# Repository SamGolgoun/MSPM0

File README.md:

# MSPM0 Development Board

A compact development board built around the **Texas Instruments MSPM0G3507** Arm Cortex-M0+ microcontroller, designed in **KiCad**. The board includes USB-to-UART communication, an I2C accelerometer, and a standard SWD header for programming and debugging.

## Features

- **MCU:** TI MSPM0G3507 (LQFP-48), Arm Cortex-M0+
- **USB-C connector** with ESD protection
- **USB-UART converter:** CH340E
- **3.3 V LDO regulator** powered from USB
- **Accelerometer:** ST LIS2DH (I2C, with interrupt lines INT1/INT2)
- **8 MHz external crystal** (HFXT)
- **SWD header** (TC2030 Tag-Connect) for programming and debugging
- Decoupling and reset circuitry following manufacturer recommendations

## Schematic

## Repository Contents

| File | Description |
|------|-------------|
| `MSPM0.kicad_sch` | Schematic |
| `MSPM0.kicad_pcb` | PCB layout |
| `MSPM0.kicad_pro` | KiCad project file |
| `MSPM0-ToturialSchemSymLib.kicad_sym` | Custom symbol library |
| `sym-lib-table` | Project symbol library table |

## Getting Started

1. Install [KiCad](https://www.kicad.org/) (developed with KiCad 10).
2. Clone this repository:
   ```bash
   git clone https://github.com/SamGolgoun/MSPM0.git
   ```
3. Open `MSPM0.kicad_pro` in KiCad.
4. Make sure the project symbol library is loaded (Preferences → Manage Symbol Libraries → Project Specific Libraries).

## Status

🚧 Work in progress: schematic complete, PCB layout and routing ongoing.

## Acknowledgements

This project was created while following the [Phil's Lab](https://www.youtube.com/@PhilsLab) KiCad hardware design tutorial for the MSPM0. Many thanks for the excellent material.

## License

This project is licensed under the [MIT License](LICENSE).

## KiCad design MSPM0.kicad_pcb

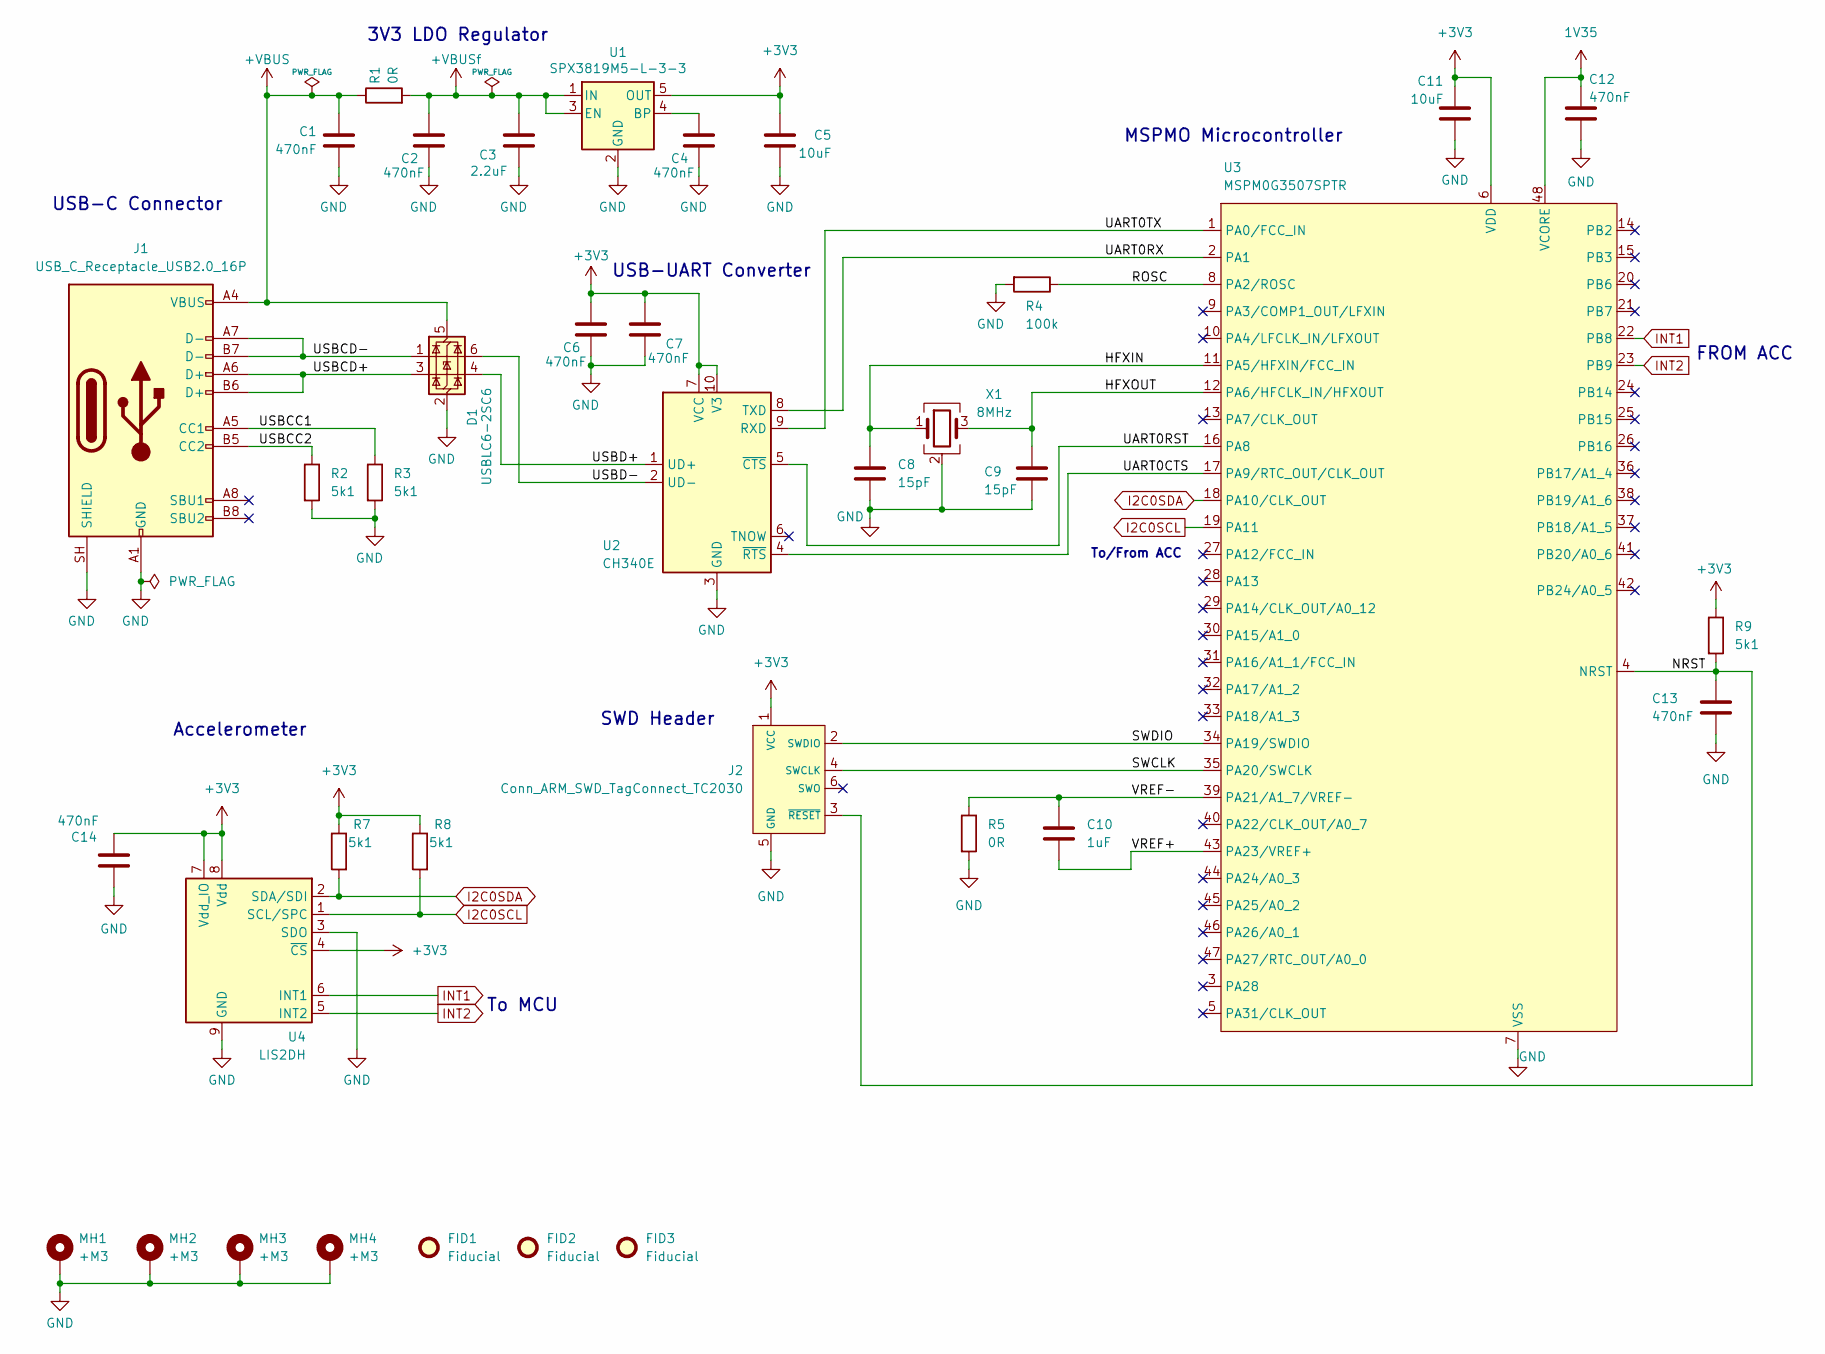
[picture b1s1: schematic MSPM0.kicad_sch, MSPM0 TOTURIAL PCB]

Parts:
C1, C2, C4, C6, C7, C12, C13, C14: 470nF; C_0603_1608Metric; Manufacturer Part Number CL10B474KA8NNNC; LCSC C1623
C3: 2.2uF; C_0805_2012Metric; Manufacturer Part Number CL21B225KAFNNNE; LCSC C19110
C5, C11: 10uF; C_0805_2012Metric; Manufacturer Part Number CL21A106KAYNNNE; LCSC C15850
C8, C9: 15pF; C_0603_1608Metric
C10: 1uF; C_0603_1608Metric; Manufacturer Part Number CL21B474KBFNNNE; LCSC C13967
D1: USBLC6-2SC6; SOT-23-6
FID1, FID2, FID3: Fiducial; Fiducial_1mm_Mask2mm
J1: USB_C_Receptacle_USB2.0_16P; USB_C_Receptacle_GCT_USB4105-xx-A_16P_TopMnt_Horizontal
J2: Conn_ARM_SWD_TagConnect_TC2030; Tag-Connect_TC2030-IDC-FP_2x03_P1.27mm_Vertical
MH1, MH2, MH3, MH4: +M3; MountingHole_3.2mm_M3_Pad_Via
R1, R5: 0R; R_0603_1608Metric
R2, R3, R7, R8, R9: 5k1; R_0603_1608Metric
R4: 100k; R_0603_1608Metric; Manufacturer Part Number RT0603BRD07100KL; LCSC C122538
U1: SPX3819M5-L-3-3; SOT-23-5
U2: CH340E; MSOP-10_3x3mm_P0.5mm
U3: MSPM0G3507SPTR; LQFP-48_7x7mm_P0.5mm; Manufacturer Part Number MSPM0G3507SPTR; LCSC C22362630
U4: LIS2DH; LGA-14_2x2mm_P0.35mm_LayoutBorder3x4y
X1: 8MHz; Crystal_SMD_3225-4Pin_3.2x2.5mm

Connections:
1V35: C12.1, U3.48 (VCORE)
+3V3: C5.1, C6.1, C7.1, C11.1, C14.1, J2.1 (VCC), R7.1, R8.1, R9.1, U1.5 (OUT), U2.7 (VCC), U2.10 (V3), U3.6 (VDD), U4.4 (~CS), U4.7 (Vdd_IO), U4.8 (Vdd)
+VBUS: C1.1, D1.5 (VBUS), J1.A4 (VBUS), J1.A9 (VBUS), J1.B4 (VBUS), J1.B9 (VBUS), R1.1
+VBUSf: C2.1, C3.1, R1.2, U1.1 (IN), U1.3 (EN)
/HFXIN: C8.1, U3.11 (PA5/HFXIN/FCC_IN), X1.1
/HFXOUT: C9.1, U3.12 (PA6/HFCLK_IN/HFXOUT), X1.3
/NRST: C13.1, J2.3 (~RESET), R9.2, U3.4 (NRST)
/ROSC: R4.1, U3.8 (PA2/ROSC)
/SWCLK: J2.4 (SWCLK), U3.35 (PA20/SWCLK)
/SWDIO: J2.2 (SWDIO), U3.34 (PA19/SWDIO)
/UART0CTS: U2.4 (~RTS), U3.17 (PA9/RTC_OUT/CLK_OUT)
/UART0RST: U2.5 (~CTS), U3.16 (PA8)
/UART0RX: U2.8 (TXD), U3.2 (PA1)
/UART0TX: U2.9 (RXD), U3.1 (PA0/FCC_IN)
/USBCC1: J1.A5 (CC1), R3.1
/USBCC2: J1.B5 (CC2), R2.1
/USBCD+: D1.3 (I/O2), J1.A6 (D+), J1.B6 (D+)
/USBCD-: D1.1 (I/O1), J1.A7 (D-), J1.B7 (D-)
/USBD+: D1.4 (I/O2), U2.1 (UD+)
/USBD-: D1.6 (I/O1), U2.2 (UD-)
/VREF+: C10.2, U3.43 (PA23/VREF+)
/VREF-: C10.1, R5.1, U3.39 (PA21/A1_7/VREF-)
GND: C1.2, C2.2, C3.2, C4.2, C5.2, C6.2, C7.2, C8.2, C9.2, C11.2, C12.2, C13.2, C14.2, D1.2 (GND), J1.A1 (GND), J1.A12 (GND), J1.B1 (GND), J1.B12 (GND), J1.SH (SHIELD), J2.5 (GND), MH1.1 (1_1), MH2.1 (1_1), MH3.1 (1_1), MH4.1 (1_1), R2.2, R3.2, R4.2, R5.2, U1.2 (GND), U2.3 (GND), U3.7 (VSS), U4.3 (SDO), U4.9 (GND), U4.10 (GND), U4.11 (GND), U4.12 (GND), U4.13 (GND), U4.14 (GND), X1.2 (G), X1.4 (G)
I2C0SCL: R8.2, U3.19 (PA11), U4.1 (SCL/SPC)
I2C0SDA: R7.2, U3.18 (PA10/CLK_OUT), U4.2 (SDA/SDI)
INT1: U3.22 (PB8), U4.6 (INT1)
INT2: U3.23 (PB9), U4.5 (INT2)
unnamed: C4.1, U1.4 (BP)

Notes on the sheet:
FROM ACC
To MCU
SWD Header
Accelerometer
To/From ACC
USB-UART Converter
3V3 LDO Regulator
USB-C Connector
MSPMO Microcontroller

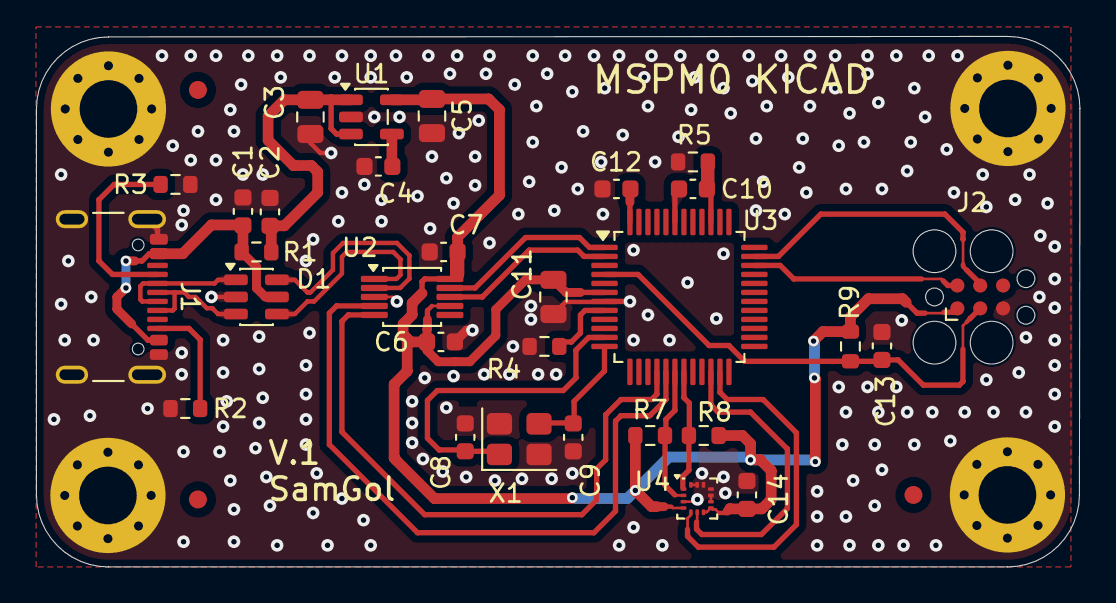
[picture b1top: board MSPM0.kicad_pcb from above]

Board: 2 copper layers, 58.0 x 29.5 mm, 37 parts (0 on the bottom side), 28 nets.
